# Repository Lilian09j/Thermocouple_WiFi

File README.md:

# Thermocouple_WiFi
Development of a type K thermocouple with wireless data acquisition via WiFi from a Java App

Cold junction temperature measured by an LM335Z, MCP6002 AOPs in differential assembly, voltage sampling with an MCP3301 14bits ADC

The components used are thoses : ESP8266 (nodeMCU), MCP3301, MCP6002 and LM335Z

JAOUANNE Lilian & GARCON Bastian

Développement d'un thermocouple de type K basé sur un ESP8266 avec acquisition WiFi depuis une application Java

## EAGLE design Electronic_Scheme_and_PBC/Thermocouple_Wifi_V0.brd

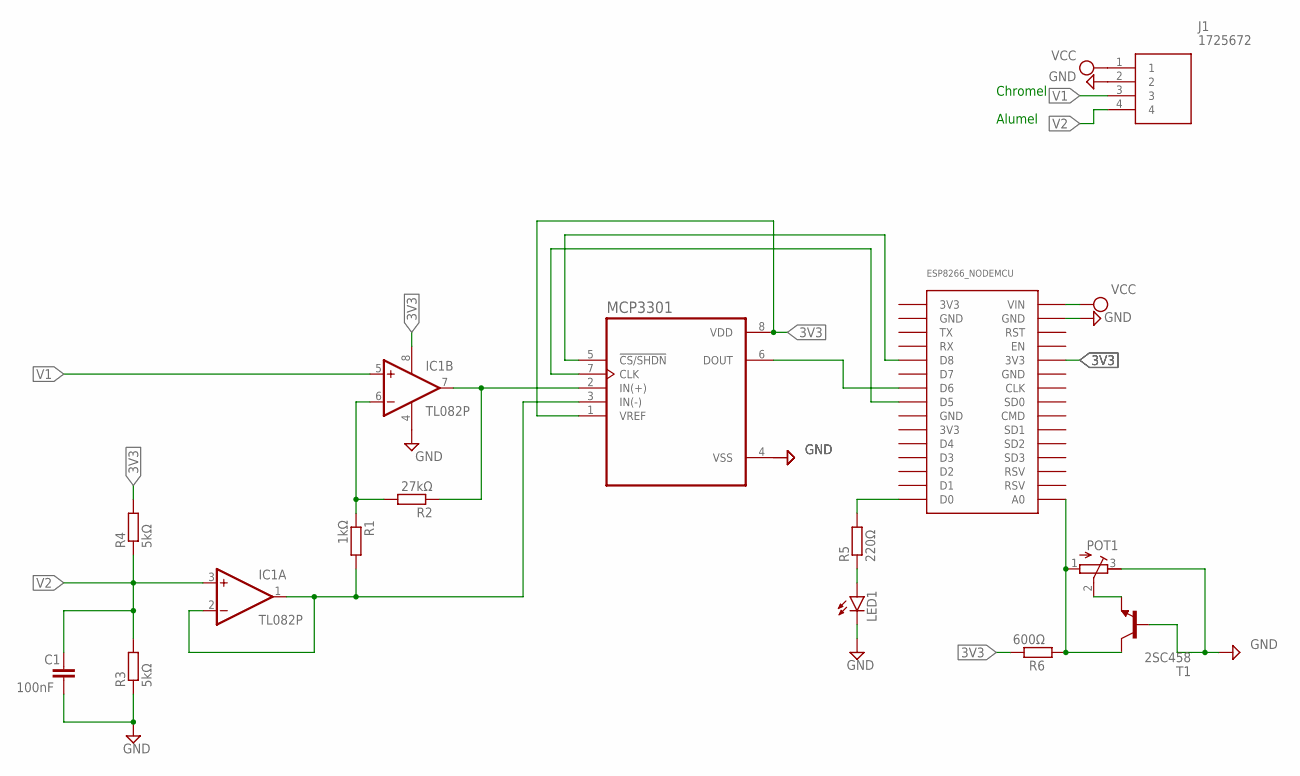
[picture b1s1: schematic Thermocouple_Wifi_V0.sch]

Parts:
C1: 100nF; C050-025X075
ESP8266_NODEMCU: NODEMCU_ESP8266
IC1: TL082P; DIL08
J1: 1725672; 1725672-4-2.54
LED1: LED5MM
MCP3301: MCP3301-CI/P; DIP787W46P254L927H533Q8
POT1: R-TRIMM74W; RTRIM74W
R1: 1kΩ; 0204/7
R2: 27kΩ; 0204/7
R3, R4: 5kΩ; 0204/7
R5: 220Ω; 0204/7
R6: 600Ω; 0204/7
T1: 2SC458; TO92-ECB

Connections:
3V3: ESP8266_NODEMCU.3V3@1 (3V3), ESP8266_NODEMCU.3V3@2 (3V3), ESP8266_NODEMCU.3V3@3 (3V3), IC1.8 (V+), MCP3301.1 (VREF), MCP3301.8 (VDD), R4.2, R6.2
GND: C1.2, ESP8266_NODEMCU.GND@1 (GND), ESP8266_NODEMCU.GND@2 (GND), ESP8266_NODEMCU.GND@3 (GND), ESP8266_NODEMCU.GND@4 (GND), IC1.4 (V-), J1.2, LED1.K (C), MCP3301.4 (VSS), POT1.3 (E), R3.1, T1.B
unnamed: ESP8266_NODEMCU.D5, MCP3301.7 (CLK)
unnamed: ESP8266_NODEMCU.A0, POT1.1 (A), R6.1, T1.C
unnamed: ESP8266_NODEMCU.D6, MCP3301.6 (DOUT)
unnamed: ESP8266_NODEMCU.D8, MCP3301.5 (!CS/SHDN)
unnamed: LED1.A, R5.1
unnamed: POT1.2 (S), T1.E
unnamed: IC1.7 (OUT), MCP3301.2 (IN(+)), R2.1
unnamed: IC1.1 (OUT), IC1.2 (-IN), MCP3301.3 (IN(-)), R1.2
unnamed: ESP8266_NODEMCU.D0, R5.2
unnamed: IC1.6 (-IN), R1.1, R2.2
V1: IC1.5 (+IN), J1.3
V2: C1.1, IC1.3 (+IN), J1.4, R3.2, R4.1
VCC: ESP8266_NODEMCU.VIN, J1.1

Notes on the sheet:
Chromel
Alumel

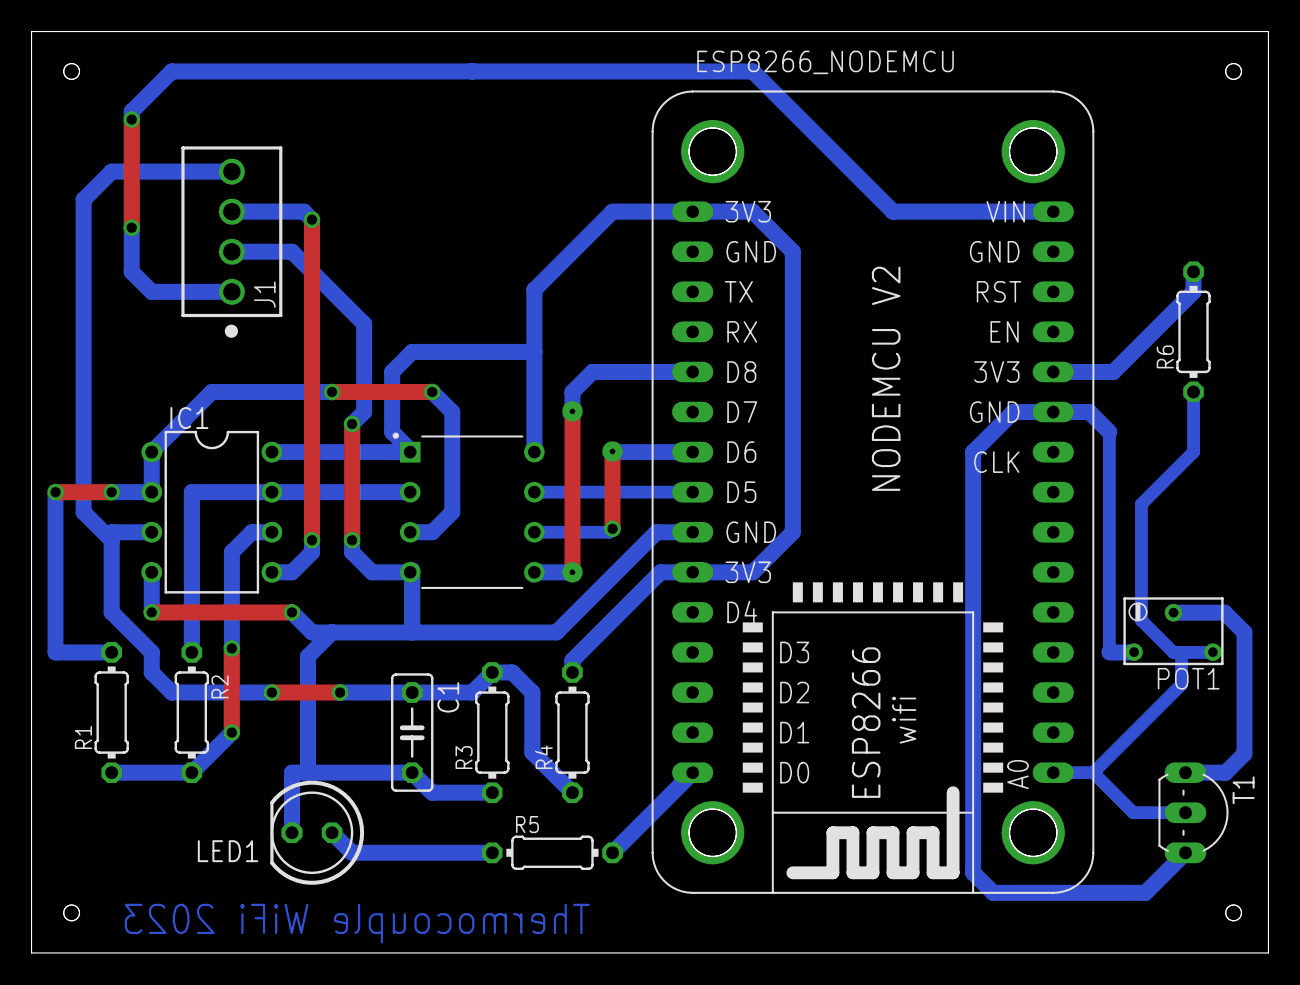
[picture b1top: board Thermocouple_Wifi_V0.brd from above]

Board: 2 copper layers, 78.4 x 58.4 mm, 14 parts (0 on the bottom side), 15 nets.
